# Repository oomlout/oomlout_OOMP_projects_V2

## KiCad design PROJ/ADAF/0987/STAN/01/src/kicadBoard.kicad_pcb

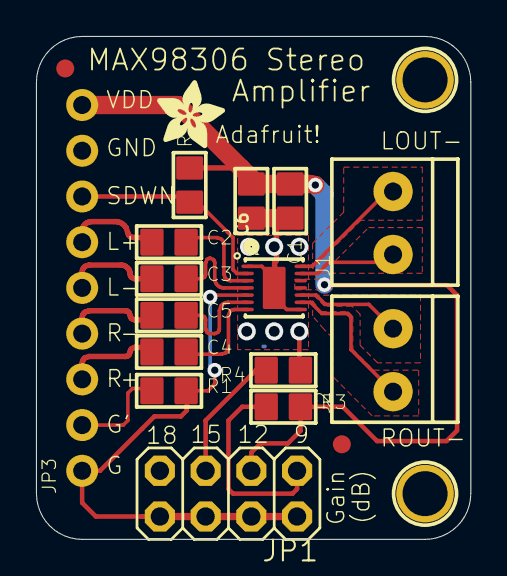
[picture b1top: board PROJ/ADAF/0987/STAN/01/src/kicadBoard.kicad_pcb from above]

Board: 2 copper layers, 24.1 x 27.9 mm, 20 parts (0 on the bottom side), 19 nets.

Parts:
C1: 0.1µF; 0805
C2, C3, C4, C5: 1µF; 0805
C6: 10µF; 0805
FID1, FID2: FIDUCIAL""; FIDUCIAL_1MM
J1: OUTL; TERMBLOCK_1X2-3.5MM
J2: OUTR; TERMBLOCK_1X2-3.5MM
JP1: 2X04
JP3: 1X09_ROUND_70
R1, R3, R4: 100K; 0805
R5: 10K; 0805
U1: MAX98306ETD+T; TDFN14_3X3MM
U$6, U$7: MOUNTINGHOLE2.5; MOUNTINGHOLE_2.5_PLATED
U$10: ADAFRUIT_3.5MM

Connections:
GAIN1: JP1.2, JP1.4, JP1.6, JP1.8, JP3.1, R1.2, U1.P$5
GAIN2: JP3.2, R1.1
GND: C1.2, C6.2, JP1.7, JP3.8, R4.1, U1.P$1, U1.P$8, U1.P$THERMAL
IN_LEFT+: C2.1, JP3.6
IN_LEFT-: C3.1, JP3.5
IN_RIGHT+: C4.1, JP3.3
IN_RIGHT-: C5.1, JP3.4
LOUT-: J1.1, U1.P$14
unnamed: JP1.1, R3.1
unnamed: C2.2, U1.P$3
unnamed: JP1.5, R4.2
unnamed: C3.2, U1.P$4
unnamed: C4.2, U1.P$7
unnamed: C5.2, U1.P$6
unnamed: J1.2, U1.P$13
unnamed: J2.2, U1.P$9
ROUT+: J2.1, U1.P$10
SHUTDOWN: JP3.7, R5.1, U1.P$2
VDD: C1.1, C6.1, JP1.3, JP3.9, R3.2, R5.2, U1.P$11, U1.P$12

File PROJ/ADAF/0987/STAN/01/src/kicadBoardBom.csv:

"Id";"Designator";"Package";"Quantity";"Designation";"Supplier and ref";
1;"C1";"0805";1;"0.1µF";;;
2;"U$10";"ADAFRUIT_3.5MM";1;"";;;
3;"R1,R3,R4";"0805";3;"100K";;;
4;"JP1";"2X04";1;"";;;
5;"J1";"TERMBLOCK_1X2-3.5MM";1;"OUTL";;;
6;"FID1,FID2";"FIDUCIAL_1MM";2;"FIDUCIAL""";;;
7;"U$7,U$6";"MOUNTINGHOLE_2.5_PLATED";2;"MOUNTINGHOLE2.5";;;
8;"C4,C5,C2,C3";"0805";4;"1µF";;;
9;"J2";"TERMBLOCK_1X2-3.5MM";1;"OUTR";;;
10;"JP3";"1X09_ROUND_70";1;"";;;
11;"R5";"0805";1;"10K";;;
12;"C6";"0805";1;"10µF";;;
13;"U1";"TDFN14_3X3MM";1;"MAX98306ETD+T";;;

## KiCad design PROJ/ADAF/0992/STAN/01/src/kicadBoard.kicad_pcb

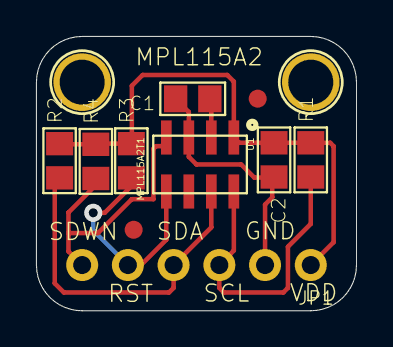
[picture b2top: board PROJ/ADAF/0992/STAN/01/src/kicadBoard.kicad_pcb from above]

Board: 2 copper layers, 17.8 x 15.2 mm, 13 parts (1 on the bottom side), 7 nets.

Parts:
C1, C2: 1µF; 0805
FID1, FID2: FIDUCIAL""; FIDUCIAL_1MM
JP1: 1X06_ROUND_70
R1, R2, R3, R4: 10K; 0805
U1: MPL115A2T1; LGA8
U$8, U$9: MOUNTINGHOLE2.5; MOUNTINGHOLE_2.5_PLATED
U$14: ADAFRUIT_3.5MM

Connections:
GND: C1.2, C2.2, JP1.2, U1.P$3
unnamed: C1.1, U1.P$2
RESET: JP1.5, R3.1, U1.P$5
SCL: JP1.3, R1.1, U1.P$8
SDA: JP1.4, R2.1, U1.P$7
SHDN: JP1.6, R4.1, U1.P$4
VDD: C2.1, JP1.1, R1.2, R2.2, R3.2, R4.2, U1.P$1

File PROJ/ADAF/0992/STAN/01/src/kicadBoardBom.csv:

"Id";"Designator";"Package";"Quantity";"Designation";"Supplier and ref";
1;"R4,R3,R1,R2";"0805";4;"10K";;;
2;"U$9,U$8";"MOUNTINGHOLE_2.5_PLATED";2;"MOUNTINGHOLE2.5";;;
3;"C2,C1";"0805";2;"1µF";;;
4;"FID2,FID1";"FIDUCIAL_1MM";2;"FIDUCIAL""";;;
5;"JP1";"1X06_ROUND_70";1;"";;;
6;"U1";"LGA8";1;"MPL115A2T1";;;
7;"U$14";"ADAFRUIT_3.5MM";1;"";;;

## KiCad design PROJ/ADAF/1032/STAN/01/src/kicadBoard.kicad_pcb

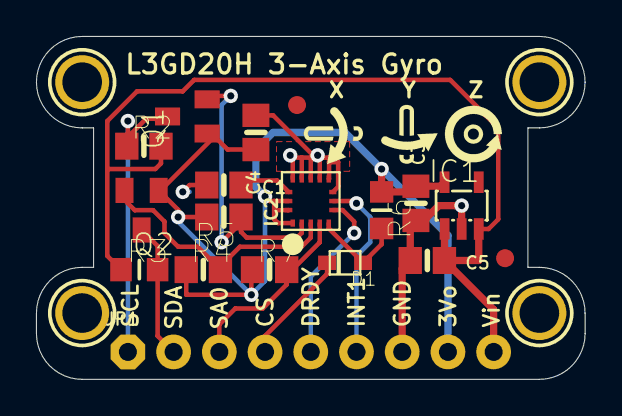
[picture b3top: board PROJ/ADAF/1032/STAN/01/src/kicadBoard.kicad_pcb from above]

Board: 2 copper layers, 30.5 x 19.0 mm, 24 parts (1 on the bottom side), 13 nets.

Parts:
C1, C4: 0.1uF; 0805-NO
C3, C5: 10uF; 0805-NO
D1: 1N4148; SOD-323F
IC1: MIC5225-3.3; SOT23-5L
IC2: LGD20H; L3GD20H_LGA16L
JP1: 1X09_ROUND_76
Q1, Q2: BSS138; SOT23
R2, R4, R5, R7: 10K; 0805-NO
R3, R6: 10K; _0805MP
U$3: SYMBOL_GYROXYZ_10MM
U$10: ADAFRUIT_TEXT_20MM
U$11, U$12, U$13, U$14: MOUNTINGHOLE2.0; MOUNTINGHOLE_2.0_PLATED
U$15, U$16: FIDUCIAL; FIDUCIAL_1MM

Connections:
+3V3: C3.2, C4.2, IC1.5, IC2.1, IC2.15, IC2.16, JP1.8, Q1.1, Q2.1, R4.1, R5.2, R6.1, R7.1
+5V: C5.2, IC1.1, IC1.3, JP1.9, R2.2, R3.1
CS_3.3V: D1.A, IC2.5, R6.2
CS_5.0V: D1.C, JP1.4
DRDY/INT2: IC2.6, JP1.5
GND: C1.1, C3.1, C4.1, C5.1, IC1.2, IC2.8, IC2.9, IC2.10, IC2.11, IC2.12, IC2.13, JP1.7
INT1: IC2.7, JP1.6
unnamed: C1.2, IC2.14
SCL/SPC_3.3V: IC2.2, Q1.2, R5.1
SCL/SPC_5.0V: JP1.1, Q1.3, R2.1
SDA/SDI/SDO_3.3V: IC2.3, Q2.2, R4.2
SDA/SDI/SDO_5.0V: JP1.2, Q2.3, R3.2
SDO/SAO: IC2.4, JP1.3, R7.2

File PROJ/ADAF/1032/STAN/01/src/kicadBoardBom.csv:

"Id";"Designator";"Package";"Quantity";"Designation";"Supplier and ref";
1;"R5,R7,R2,R4";"0805-NO";4;"10K";;;
2;"U$16,U$15";"FIDUCIAL_1MM";2;"FIDUCIAL";;;
3;"U$12,U$11,U$14,U$13";"MOUNTINGHOLE_2.0_PLATED";4;"MOUNTINGHOLE2.0";;;
4;"R3,R6";"_0805MP";2;"10K";;;
5;"Q1,Q2";"SOT23";2;"BSS138";;;
6;"U$3";"SYMBOL_GYROXYZ_10MM";1;"";;;
7;"JP1";"1X09_ROUND_76";1;"";;;
8;"D1";"SOD-323F";1;"1N4148";;;
9;"C5,C3";"0805-NO";2;"10uF";;;
10;"IC1";"SOT23-5L";1;"MIC5225-3.3";;;
11;"C4,C1";"0805-NO";2;"0.1uF";;;
12;"IC2";"L3GD20H_LGA16L";1;"LGD20H";;;
13;"U$10";"ADAFRUIT_TEXT_20MM";1;"";;;

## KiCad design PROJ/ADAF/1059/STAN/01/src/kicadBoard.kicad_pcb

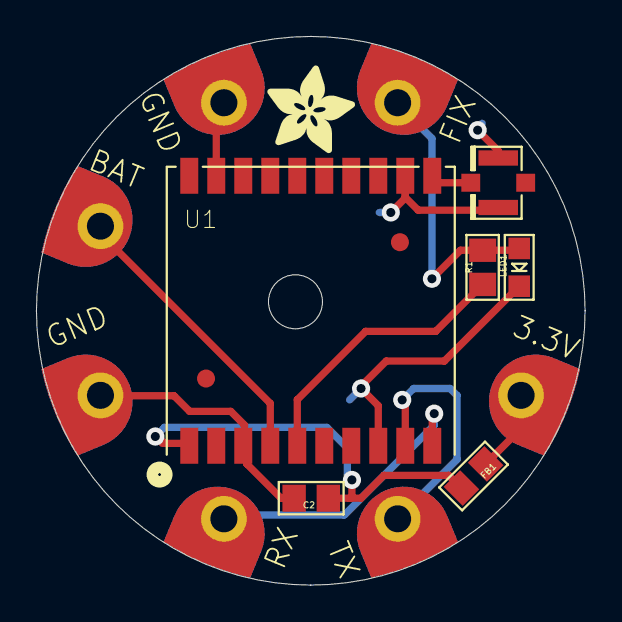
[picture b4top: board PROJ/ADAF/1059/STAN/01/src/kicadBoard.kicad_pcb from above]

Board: 2 copper layers, 30.5 x 30.5 mm, 17 parts (1 on the bottom side), 9 nets.

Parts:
C2: 10uF; 0805
FB1: Ferrite; 0805
FID1, FID2: FIDUCIAL""; FIDUCIAL_1MM
GND0, GND1: SEWTAP-2.0IN; SEWINGTAP_2.0
LED1: FIX; CHIPLED_0805
R1: 1K; 0805
RX0: SEWTAP-2.0IN; SEWINGTAP_2.0
TP1, TP4: SEWTAP-2.0IN; SEWINGTAP_2.0
TX0: SEWTAP-2.0IN; SEWINGTAP_2.0
U1: FGPMMOPA6H
U$6: ADAFRUIT_5MM
U$7: FLORASMALL
U$20: U.FL
UNK3V3IN0: SEWTAP-2.0IN; SEWINGTAP_2.0

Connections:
3.3V: C2.1, FB1.2, U1.P$1
GND: C2.2, GND0.P$1, GND1.P$1, LED1.C, U1.P$3, U1.P$8, U1.P$12, U1.P$19, U$20.P$1, U$20.P$2
unnamed: LED1.A, R1.1, TP4.P$1
unnamed: R1.2, U1.P$5
unnamed: FB1.1, UNK3V3IN0.P$1
unnamed: U1.P$11, U$20.P$3
RX: RX0.P$1, U1.P$10
TX: TX0.P$1, U1.P$9
VBACKUP: TP1.P$1, U1.P$4

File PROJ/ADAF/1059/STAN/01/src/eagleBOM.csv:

"Part";"Value";"Device";"Package";"Description";"";
"3V3IN";"SEWTAP-2.0IN";"SEWTAP-2.0IN";"SEWINGTAP_2.0";"";"";
"C2";"10uF";"CAP_CERAMIC0805";"0805";"Ceramic Capacitors";"";
"FB1";"Ferrite";"FERRITE0805";"0805";"Ferrite Bead";"";
"FID1";"FIDUCIAL""";"FIDUCIAL""";"FIDUCIAL_1MM";"Fiducial Alignment Points";"";
"FID2";"FIDUCIAL""";"FIDUCIAL""";"FIDUCIAL_1MM";"Fiducial Alignment Points";"";
"GND";"SEWTAP-2.0IN";"SEWTAP-2.0IN";"SEWINGTAP_2.0";"";"";
"GND1";"SEWTAP-2.0IN";"SEWTAP-2.0IN";"SEWINGTAP_2.0";"";"";
"LED1";"FIX";"LED0805";"CHIPLED_0805";"LED";"";
"R1";"1K";"RESISTOR0805";"0805";"Resistors";"";
"RX";"SEWTAP-2.0IN";"SEWTAP-2.0IN";"SEWINGTAP_2.0";"";"";
"TP1";"SEWTAP-2.0IN";"SEWTAP-2.0IN";"SEWINGTAP_2.0";"";"";
"TP4";"SEWTAP-2.0IN";"SEWTAP-2.0IN";"SEWINGTAP_2.0";"";"";
"TX";"SEWTAP-2.0IN";"SEWTAP-2.0IN";"SEWINGTAP_2.0";"";"";
"U$20";"U.FL";"U.FL";"U.FL";"U.FL Antenna Connector";"";
"U1";"FGPMMOPA6H";"GPS_FGPMMOPA6H";"FGPMMOPA6H";"GPS Module - MTK MT3339 Chipset, -165dBm sensitivity, 22 channels, 10Hz, auto-select external antenna options";"";

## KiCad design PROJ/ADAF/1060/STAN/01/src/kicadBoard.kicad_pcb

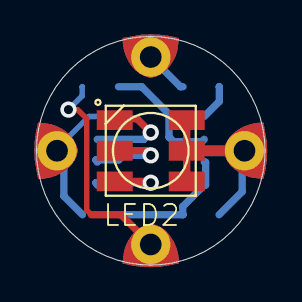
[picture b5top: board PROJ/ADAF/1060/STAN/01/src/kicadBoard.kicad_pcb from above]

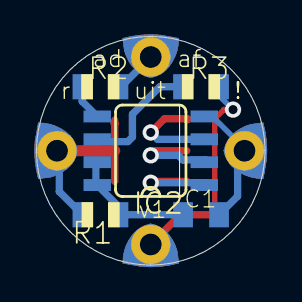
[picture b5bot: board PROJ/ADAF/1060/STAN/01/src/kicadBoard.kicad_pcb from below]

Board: 16 copper layers, 12.7 x 12.7 mm, 10 parts (5 on the bottom side), 10 nets.

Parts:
C1: 1uF; C0805K
DATA_INPUT0: SEWTAP0.5IN; SEWINGTAP_0.5
DATA_OUTPUT0: SEWTAP0.5IN; SEWINGTAP_0.5
GND0: SEWTAP0.5IN; SEWINGTAP_0.5
IC2: WS2811-SOP8; SO08-SKINNYPADS
LED2: RGBLED5050
R1: 1.0K; R0805
R2, R3: 22; R0805
VDD0: SEWTAP0.5IN; SEWINGTAP_0.5

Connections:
GND: C1.2, GND0.TAP, IC2.4
unnamed: IC2.3, LED2.4
unnamed: IC2.2, LED2.5
unnamed: IC2.1, LED2.6
unnamed: IC2.6, R3.1
unnamed: IC2.5, R2.1
unnamed: DATA_INPUT0.TAP, R3.2
unnamed: DATA_OUTPUT0.TAP, R2.2
unnamed: C1.1, IC2.7, IC2.8, R1.1
VDD: LED2.1, LED2.2, LED2.3, R1.2, VDD0.TAP

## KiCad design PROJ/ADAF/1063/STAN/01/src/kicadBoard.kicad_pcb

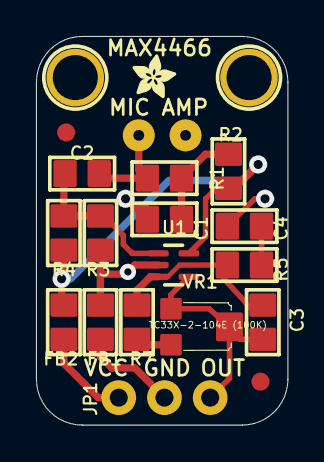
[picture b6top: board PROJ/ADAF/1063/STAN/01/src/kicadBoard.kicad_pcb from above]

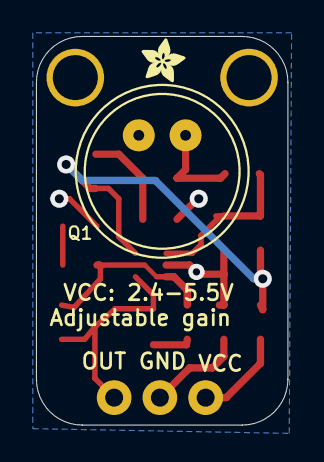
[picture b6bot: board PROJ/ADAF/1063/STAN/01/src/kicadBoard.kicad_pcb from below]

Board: 2 copper layers, 14.0 x 21.6 mm, 22 parts (2 on the bottom side), 11 nets.

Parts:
C1: 0.1µF; 0805
C2: 0.01uF; 0805
C3: 100pF; 0805
C4: 10uF; 0805
FB1, FB2: FERRITE; 0805
FID1, FID2: FIDUCIAL""; FIDUCIAL_1MM
JP1: 1X03_ROUND_76
Q1: CMA-4544PF-W; ELECTRET_9.7
R1, R2, R5: 1K; 0805
R3, R4: 1M; 0805
R7: 22K; 0805
U1: MAX4466EXK+T; SC70-5
U$11, U$14: MOUNTINGHOLE2.5; MOUNTINGHOLE_2.5_PLATED
U$16, U$17: ADAFRUIT_2.5MM
VR1: TC33X-2-104E (100K); TRIMPOT_BOURNS_TC33X-2

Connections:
AGND: C1.2, C4.2, FB1.2, Q1.-, R3.1, U1.2
AVCC: FB2.1, R2.2, R4.2, U1.5
GND: FB1.1, JP1.2
unnamed: C3.2, R5.2, R7.1, U1.3
unnamed: R7.2, VR1.3
unnamed: C2.1, Q1.+, R1.1
unnamed: C1.1, R1.2, R2.1
unnamed: C2.2, R3.2, R4.1, U1.1
unnamed: C3.1, JP1.3, U1.4, VR1.1, VR1.2
unnamed: C4.1, R5.1
VCC: FB2.2, JP1.1

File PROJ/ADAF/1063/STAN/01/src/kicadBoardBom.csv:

"Id";"Designator";"Package";"Quantity";"Designation";"Supplier and ref";
1;"R4,R3";"0805";2;"1M";;;
2;"U$16,U$17";"ADAFRUIT_2.5MM";2;"";;;
3;"FB2,FB1";"0805";2;"FERRITE";;;
4;"R1,R2,R5";"0805";3;"1K";;;
5;"FID1,FID2";"FIDUCIAL_1MM";2;"FIDUCIAL""";;;
6;"JP1";"1X03_ROUND_76";1;"";;;
7;"U$14,U$11";"MOUNTINGHOLE_2.5_PLATED";2;"MOUNTINGHOLE2.5";;;
8;"U1";"SC70-5";1;"MAX4466EXK+T";;;
9;"VR1";"TRIMPOT_BOURNS_TC33X-2";1;"TC33X-2-104E (100K)";;;
10;"R7";"0805";1;"22K";;;
11;"C2";"0805";1;"0.01uF";;;
12;"C4";"0805";1;"10uF";;;
13;"C3";"0805";1;"100pF";;;
14;"C1";"0805";1;"0.1µF";;;
15;"Q1";"ELECTRET_9.7";1;"CMA-4544PF-W";;;

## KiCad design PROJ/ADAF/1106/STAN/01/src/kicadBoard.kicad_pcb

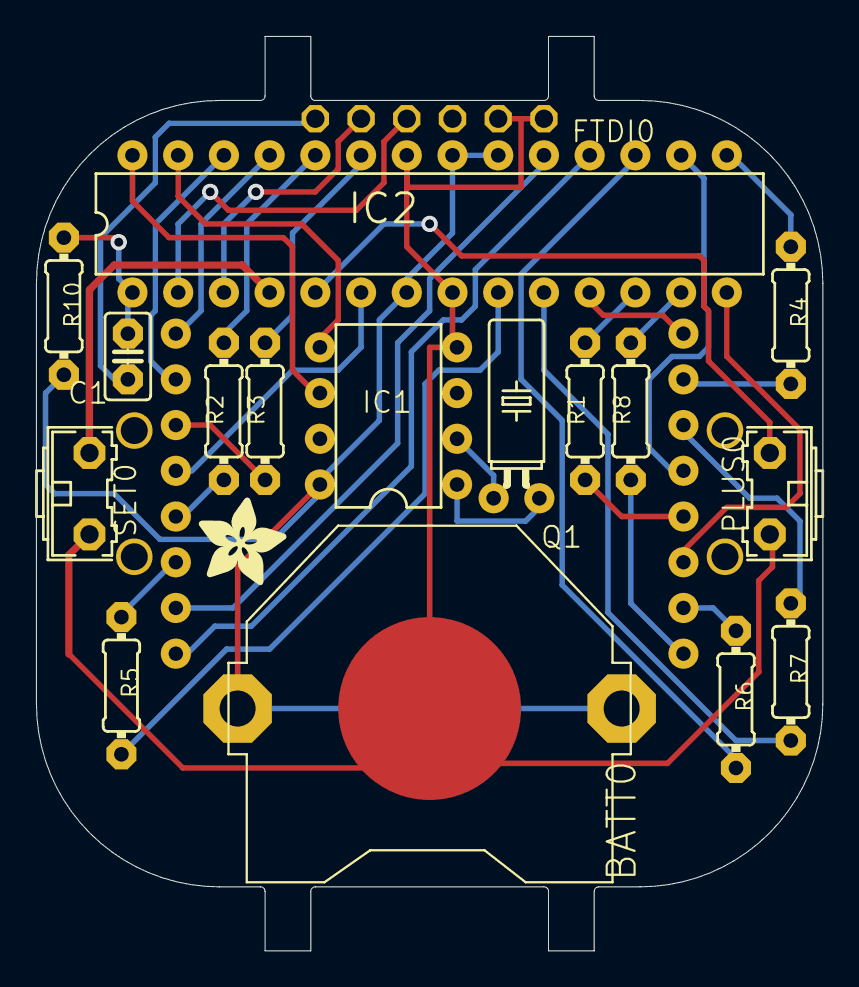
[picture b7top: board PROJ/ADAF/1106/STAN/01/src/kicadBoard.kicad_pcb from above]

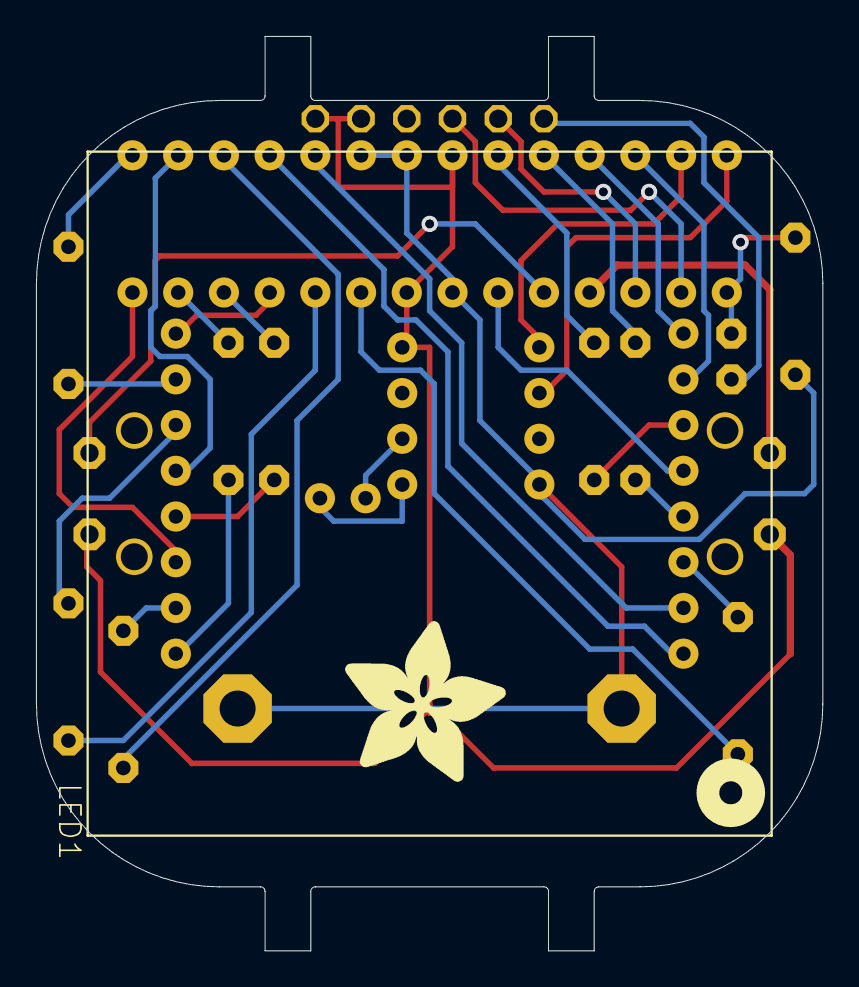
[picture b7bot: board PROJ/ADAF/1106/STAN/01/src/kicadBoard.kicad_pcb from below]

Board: 16 copper layers, 43.7 x 50.8 mm, 20 parts (2 on the bottom side), 36 nets.

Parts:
BATT0: CR2032; CR2032-THRU
C1: 0.1uF; C025-025X050
FTDI0: DNP; 1X06-CLEAN
IC1: DS1337; DIL08-ROUND
IC2: ATMEGA168PROUND; DIL28-3-ROUND
LED1: BL-M15881B; SEGMENT_BL-M15A881
PLUS0: B3F-31XX-SKINNIER
Q1: 32.768KHz; TC38H
R1, R2, R3, R4, R5, R6, R7, R8: 47; 0204_7
R10: 10K; 0204_7
SET0: B3F-31XX-SKINNIER
U$1: ADAFRUIT_5MM
U$2: ADAFRUIT_9MM

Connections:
GND: BATT0.-, FTDI0.1, FTDI0.2, IC1.4, IC2.8, IC2.22, PLUS0.1, SET0.2
I2C_SCL: IC1.6, IC2.28
I2C_SDA: IC1.5, IC2.27
LEDANODE0: LED1.13, R1.2
LEDANODE1: LED1.3, R5.2
LEDANODE2: LED1.4, R2.2
LEDANODE3: LED1.10, R4.2
LEDANODE4: LED1.6, R3.2
LEDANODE5: LED1.11, R7.2
LEDANODE6: LED1.15, R6.2
LEDANODE7: LED1.16, R8.2
LEDCATHODE0: IC2.11, LED1.9
LEDCATHODE1: IC2.14, LED1.14
LEDCATHODE2: IC2.25, LED1.8
LEDCATHODE3: IC2.16, LED1.12
LEDCATHODE4: IC2.18, LED1.1
LEDCATHODE5: IC2.26, LED1.7
LEDCATHODE6: IC2.19, LED1.2
LEDCATHODE7: IC2.6, LED1.5
unnamed: C1.2, IC2.1, R10.2
unnamed: IC1.1, Q1.2
unnamed: IC1.2, Q1.1
unnamed: IC2.4, SET0.1
unnamed: IC2.5, PLUS0.2
unnamed: IC2.12, R1.1
unnamed: IC2.23, R3.1
unnamed: IC2.9, R5.1
unnamed: IC2.10, R7.1
unnamed: IC2.24, R2.1
unnamed: IC2.17, R6.1
unnamed: IC2.13, R8.1
unnamed: IC2.15, R4.1
unnamed: C1.1, FTDI0.6
RXD: FTDI0.4, IC2.2
TXD: FTDI0.5, IC2.3
VCC: BATT0.+1, BATT0.+2, IC1.8, IC2.7, IC2.20, IC2.21, R10.1
